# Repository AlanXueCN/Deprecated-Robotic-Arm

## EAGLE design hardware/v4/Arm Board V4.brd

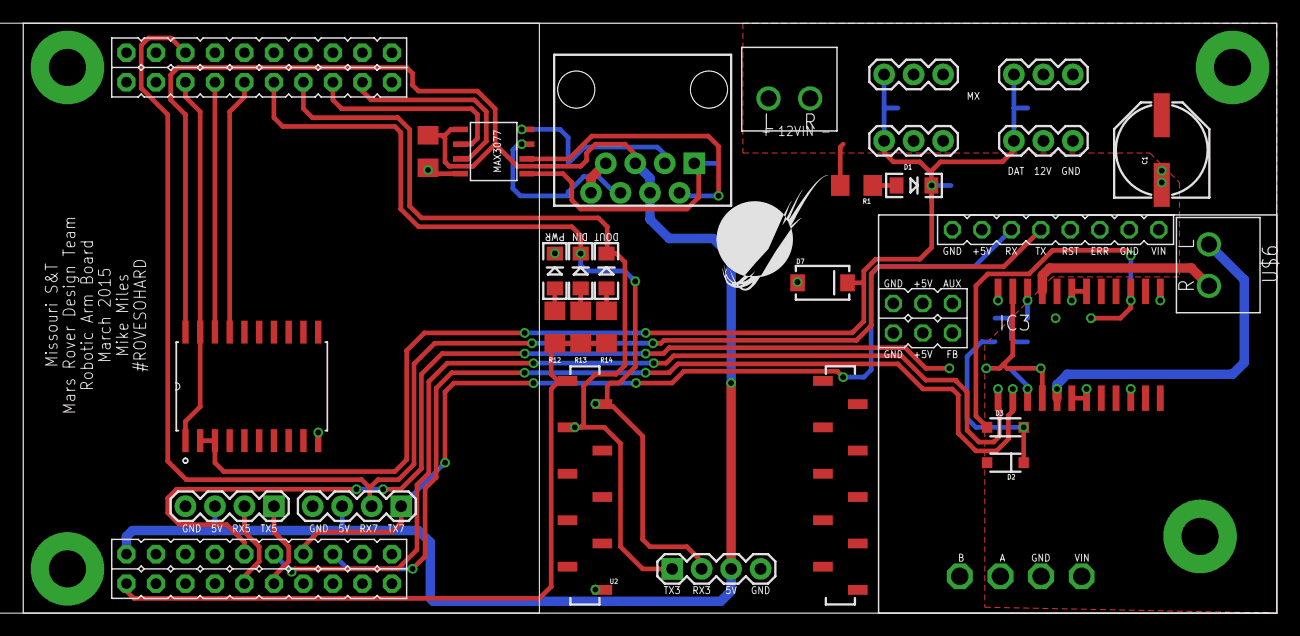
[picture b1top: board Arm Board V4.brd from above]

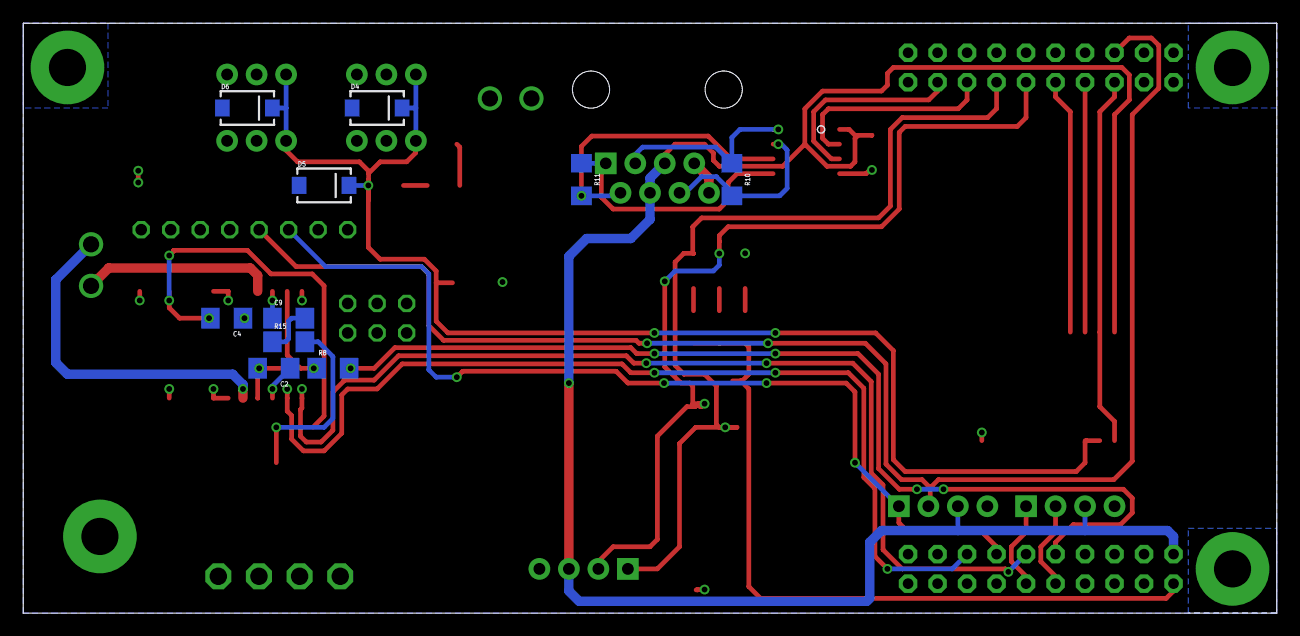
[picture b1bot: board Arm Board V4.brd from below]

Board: 2 copper layers, 108.0 x 50.8 mm, 43 parts (11 on the bottom side), 34 nets.

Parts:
C1: 330uF; PANASONIC_E
C2: 5.6nF; 1206
C4: 220nF; 1206
C9: 10nF; 1206
C12: .1uF; 1206
D1: RED; LED-1206
D2, D3: 1N4148; SOD-123
D4, D5, D6, D7: SMAJ5920; SMA-DIODE
IC3: L6206D; SO24
JP1, JP2, JP3: 1X04
JP9, JP10, JP11, JP12: DYNAMIXEL-1X03
LED1, LED2: RED; LED-1206
LED3: GREEN; LED-1206
P1: STELLARIS-LAUNCHPADSTELLARIS-LAUNCHPAD-XL; LAUNCHPAD-XL
R1, R12, R13, R14: 1k; 1206
R8: 100k; 1206
R10, R11: 120 Ohm; 1206
R15: 100; 1206
S1, S2, S3, S4: STANDOFF_ELECTRICAL; STANDOFF-ELECTRICAL
U1: SN74LS241DW; SOIC127P1030X265-20N
U2: XBEE-1B3; XBEE-SMD
U$1: TORXIS_BREAKOUT
U$3: RJ45-8PTH; RJ45-8
U$4: MAX3077; MAX3070E
U$6, U$7: H_WR-TBL_321*0002VERT; 691321100002

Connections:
+3V3: P1.3.3V, R12.2, R13.1, R14.1, U2.1
+5V: C12.1, JP1.3, JP2.3, JP3.3, P1.VBUS, U1.20, U$3.4, U$3.5, U$4.VCC
+12V: C1.+, C4.1, D2.A, IC3.17, IC3.20, JP9.VIN, JP10.VIN, JP11.VIN, JP12.VIN, R1.2, U$1.VIN, U$7.L
A1: IC3.5, U$6.L
A2: IC3.21, U$6.R
DC_1: P1.PB3, U1.1, U1.19
DDATA_1: D1.C, D4.C, D5.C, D6.C, D7.C, JP9.DDATA, JP10.DDATA, JP11.DDATA, JP12.DDATA, U1.2, U1.3
EN_A: P1.PD2, R8.2
GND: C1.-, C2.1, C12.2, D4.A, D5.A, D6.A, D7.A, IC3.3, IC3.6, IC3.7, IC3.10, IC3.13, IC3.18, IC3.19, IC3.24, JP1.4, JP2.4, JP3.4, JP9.GND, JP10.GND, JP11.GND, JP12.GND, LED1.C, P1.GND1, P1.GND2, S1.P1, S2.P1, S3.P1, S4.P1, U1.10, U2.10, U$1.GND@1, U$3.7, U$3.8, U$4.GND, U$7.R
IN1_A: IC3.1, P1.PD3
IN2_A: IC3.2, P1.PE2
unnamed: LED2.A, R13.2
unnamed: LED3.A, R14.2
unnamed: D1.A, R1.1
unnamed: D2.C, D3.A, R15.2
unnamed: C9.2, R15.1
unnamed: C9.1, IC3.22
unnamed: LED1.A, R12.1
OCD_A: C2.2, IC3.4, IC3.23, R8.1
RX+: R10.1, U$3.3, U$4.A
RX-: R10.2, U$3.6, U$4.B
RX_1: P1.PC4, U1.18
RX_2: P1.PD6, U$4.RO
RX_3: JP1.2, LED2.C, P1.PC6, U2.2
RX_5: JP3.2, P1.PE4
RX_7: JP2.2, P1.PE0, U$1.TX
TX+: R11.2, U$3.1, U$4.Y
TX-: R11.1, U$3.2, U$4.Z
TX_1: P1.PC5, U1.17
TX_2: P1.PD7, U$4.DI
TX_3: JP1.1, LED3.C, P1.PC7, U2.3
TX_5: JP3.1, P1.PE5
TX_7: JP2.1, P1.PE1, U$1.RX
VBOOT: C4.2, D3.C, IC3.15

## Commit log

2015-01-25 Revert "(in progress) arm program, board V3"
    This reverts commit 1299dbc9b697705eb9255f14b98661074306b1fd.
2015-01-25 V3 and affected structures
    a hopefully almost maybe finished V3
2015-01-25 adding the non debug version
    forgot this one
2015-01-27 Arm V3
    (Mostly) Functional code for the arm for the V3 board. All the GPIO
    functions are verified working, the UART is not working with RS-485 like
    last year, it needs debugging (converting to software serial as a
    preemptive guess).
2015-02-08 Fixed arm cod
    It works
2015-02-14 Pushing current files for V4
    V4 is in decent shape but has yet to be approved by final tests.
    Work has begun on V4_2 in the meantime, which is just adding in the
    other necessary things on top of a working arm such as the endefector
    communication.
2015-02-15 Updated structs and struct_xfer again
    On the request of motherboard, structs has a new struct and struct_xfer
    now works better and more general
2015-02-15 Catching up to master branch
2015-02-16 Moving this from google drive
2015-02-16 V4_2 passed initial tests (sends itself uart fine)
    Needs another device to send it UART instead for final test completion
    Also modified struct_xfer for arm specific purposes. Do not use for
    general usage, get that from the new_struct_xfer folder under software
    instead
2015-02-16 V4_2 final tests passed, new struct_xfer is a definite go
2015-02-23 Oops forgot something all good now
2015-02-24 Modified for VMware
    Changed constants around to be run on the virtual machine. Though note
    that you still have to preinclude stdbool.h and stdint.h in CCS
2015-02-24 Added the ability to motherboard communicate to V4
2015-03-07 reworking arm board
2015-03-09 Updated stuffs
2015-03-09 still reworking arm board
2015-03-09 okay i think im done reworking arm board
2015-03-09 okay now im done
2015-03-09 added refs
    added BOM, jrk motor controller ds
2015-03-09 arm board
    added parts to allow h-bridge actuator drive
2015-03-10 arm board
    added parts to allow linear actuator control with H-bridge in case servo
    driver fails
2015-03-10 update bom
2015-03-13 about to reroute brd
2015-03-13 didnt do much
2015-03-14 cleaned up routes, swapped 603 LEDs for 1206
2015-03-16 asdf
2015-03-16 cleaned up robo arm a bit
2015-03-16 added cap
2015-03-16 added cap, rerouted
2015-03-16 reroute ethernet port
2015-03-17 cleaned up brd, updated bom
2015-03-17 deleted old bom
2015-03-18 Added TVS diodes on Dyna data lines
    Also added parts to BOM
2015-04-10 Updated for VMWare. Cleaned organization up
    Updated for VMWare. Cleaned organization up
2015-04-10 Updating for V4_3
    Realized the arm's physical system was incapatible with previous way of
    manipulating it. Updating it for practical use
2015-04-11 Updating V4_2, on and off vmware
    added in actuator finalized capabilities. Also touched everything up, as
    some versions were missing details from other versions
2015-04-16 open loop allowed wrist and elbow vertical motion
2015-04-16 shuffling stuff around
2015-04-16 Modified struct_Xfer for sending with newprotocol
2015-04-17 Test-confirmed version
    This version of the code changes how the movement structures for
    vertically moving the wrist and the elbow work, sprinkling delays
    around. Confirmed in testing to work on the arm with this version of
    code, arm moved up and down as told. Presumably base as well, but it
    wasn't actually tested as the dynamixel was having...issues
2015-04-18 attempting to try out this whole git shell thing. Gah.
2015-04-18 Creating software development branch
    This branch is where you can find the newest work, for better or worse.
    If you want the latest versions, use this, though no garuantee that it
    works yet (though hopefully compiles).
2015-04-19 Added dynoTurn and a few while loops in the main
    void dynoTurn(uint32_t uart, uint8_t id, bool side, uint16_t Speed) -
    Servomotor rotates to the right or left and the speed indicated only if
    in continuous rotation mode.
    Added while loops that will keep movement in the desired direction until
    a new command is received NOTE BEFORE USING THIS DO NOT FORGET TO STOP
    THE DYNAMIXEL
2015-04-19 added a comment line
2015-04-19 pretty sure reset didn't need that
2015-04-20 Added in the actual implementation of the new dynoturn function and changed the prototypes of the functions that use it.
2015-04-20 sdlfkjask
2015-04-20 fjkasdjhfk
2015-04-21 Changed the struct_Xfer so we now actually read the checksum ¬_¬ Also commented in a speed variable for the arm struct, we should get it implemented in the next week so they can send us varying speeds
2015-04-22 alright this didnt save last time for some reason. So here it is instead
2015-04-22 Implemented loop in main loop function calls so it hopefully works So I put a do while loop in each of the function calls in our whole if-else thing in the main loop, so that now it will wait to exit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
2015-04-22 see my last commit 2 commits ago for info, this is just reverting to that
2015-04-22 forgot to take a useless line out.
2015-04-22 Completed the updates to receive Protocol (CSum still offline). So now the protocol will operate as follows: We get a command, and we set the dynos to do it. We continue to do it until we get a new c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
2015-04-23 All positional vectors good and functions tested. Ready for final test. All we need now is to get another board talking to this and see if it moves as we want it to.
2015-04-23 Added in more Dynamixel functions for perusing
2015-04-24 accidentally took initHardware out. Back in now
2015-04-25 Attempting to re-enable the checksum. Code in place yet untested I just switched the non blocking commands with blocking commands, so that we wait for their commands to finish coming. Might have been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
2015-04-25 Changed how comparitor works. Arm now moves, if not optimally. Checksum went back to being disabled. Arm will respond to base station commands, though still does annoying start-stop. No idea if that'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
2015-04-25 Added the variable speed UNTESTED
2015-04-26 Updated the struct id define UNTESTED
2015-04-26 Changed sizeof macro still debugging
2015-04-26 got Variable speed working. Also changed a few little things. Size defines are now macros and reset got taken out of arm.
2015-04-26 Create new project from RTOS base. No functionality yet.
2015-04-27 Add standard headers
2015-04-27 Begin porting in standard headers
2015-04-27 Start basic framework
2015-04-27 Map Uarts
2015-04-27 Add Physical Location of GPIO
2015-04-27 Dynamixel Directions fixed
2015-04-27 File Architecture, should be mostly renames
2015-04-27 Added config for GPIO UNTESTED
2015-04-27 Added Uart config
2015-04-27 UART tester code. UARTS 2 and 7 not working.
2015-04-27 Uart1 thru Uart4 all verified to transmit...that's enough tp dev for now
2015-04-27 added some trace names
2015-04-28 Fixed the Uarts...uart0 and uart6 are physically unavailable, 1-5 and 7 now TX
2015-04-28 Baud Rate sipport TESTED
2015-04-28 Stubbed out the first dynamixel send NOT FUNCTIONAL
2015-04-28 Fighting the compile FAILING
2015-04-28 Finished Architecture, Clean Compiles....UNTESTED
2015-04-28 Set Endless and full Architecture TESTED
2015-04-28 Cleaned, Commented, with TODO starting dynamixel.c
2015-04-28 A little extra commenting
2015-04-29 Added setSpeed command TESTED
2015-04-29 Tester To Move Dynamixels Endlessly...Rampes from 10 to 900 in speed and resets
2015-04-29 Clockwise, Reverse Clockwise, and Linear Actuator Support SEMI TESTED
2015-04-30 Doesn't Compile, but fully implemented
2015-04-30 Compiles UNTESTED
2015-05-01 changed e_stop_arm in structs.h to match base
2015-05-01 Validating, added 10% speed support and fixed some sys prints...something wrong with Lin actuator, dynamixel looks good
2015-05-01 Software Validation of Base to Mob to Arm...Ready for PHYSICAL TESTINg of dynamixels (Lin Act NOT ready)
2015-05-01 It's too late at night I am breaking stuff
2015-05-01 Pointers all the way down
2015-05-03 rearchitected and added module tests UNTESTED
2015-05-03 Missed a compile error deep in the tester, had to dig through make log, CCS didn't flag it
2015-05-03 Ready to Unit Test
2015-05-03 Testing End to End in Software
2015-05-03 Swapped the roboticArm task in the cfg for end to end test
2015-05-03 Took out all debug attempting to benchmark uarts
2015-05-03 Turning the Tristate Buffer to high forever right now (Uart is buffered, so we need a hook to keep from turning off too soon)
2015-05-07 Fixed the checksum and optimized argument passing/ VALIDATED in software, needs hardware testing
2015-05-08 Inverted Elbow driections per the wiring
2015-05-08 Added Gripper Support
2015-05-08 Speed at 50%
2015-05-09 Switched to Speed control for lin actuator
2015-05-09 Fixed zero speed bug
2015-05-09 Added Set Endless init for gripper
2015-05-09 Added set speed zero for gripper init
2015-05-10 fixed RX/TX issue between Tiva C and Pololu Jrk 21v3
2015-05-16 Changed baud rate for gripper for Nathan
2015-05-16 Added Drill Support UNTESTED
2015-05-16 fixed DRILL_ID bug
2015-05-18 Writes three uart streams of gps, science, bms to mob with an infintely increasing delay between writes
2015-05-19 Physical Test debugging...looks like the last mereg left in a sys print and removed some return statement
2015-05-19 Debugging Hardware
2015-05-20 Still debugging....explicit returns, protective ifs
2015-05-20 Base Speed way to fast, lowered by factor of 10
2015-05-20 Added a few System Prints in the error case for debugging
2015-05-22 Scaled Base down to +-50 speed
2015-05-22 Added Drill back
2015-05-23 Added Watchdog
2015-05-23 Take out ALL flushes and delays (debugging uart speed on error cases)
2015-05-23 Added microsecond delay support
2015-05-23 Implemented a software counter debugging inconsistent sys_clock delay times
2015-05-23 Buffers 14 messages of size 40 bytes in a rtos nailbox queue object
2015-05-24 Added rtos headers for mailbox obj
2015-05-24 Using ms_delay(1) after ever deviceWrite again
2015-05-24 Switched to us_delay(500) after ever deviceWrite
2015-05-24 us_delay(250) and it works for base 90
2015-05-26 Dynamixel Write Delay at 500 us
2015-05-26 added max/min speed protection for grippeer
2015-05-26 Prevent crash when messages are sent faster than dynamixels can process
2015-05-26 Arm delays are now based on RTOS clock.
    Major stability improvement
2015-05-27 Hack for a uart watcher task in case we can't figure out the rtos watchdog timer
2015-05-27 Uart Periodic Timeout
2015-05-28 Add watchdog
2015-05-29 reset now resets the torque limit stall ou light
2015-05-29 Disables Torque mode and re-enables in real time (hack for torque overload in the field)
2015-05-29 Added Totque mode on and torque mode off commands
2015-07-11 Added torqueEnable : untested
2015-08-09 update for erc drill linact xbee combo
2015-09-03 added lin act
2015-09-04 Drill: Add input filtering

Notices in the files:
parts and their libraries:
SparkFun-Capacitors: Licensing: Creative Commons ShareAlike 4.0 International - https://creativecommons.org/licenses/by-sa/4.0
SparkFun-Connectors: Licensing: CC v3.0 Share-Alike You are welcome to use this library for commercial purposes.
